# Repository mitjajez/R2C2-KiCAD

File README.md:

R2C2 - RepRapCncController ver. KiCAD
==========

Original design made by FMendes75@gmail.com

https://github.com/bitboxelectronics/R2C2_Hardware/blob/master/v1.2/R2C2_v1.2_Schematics.pdf

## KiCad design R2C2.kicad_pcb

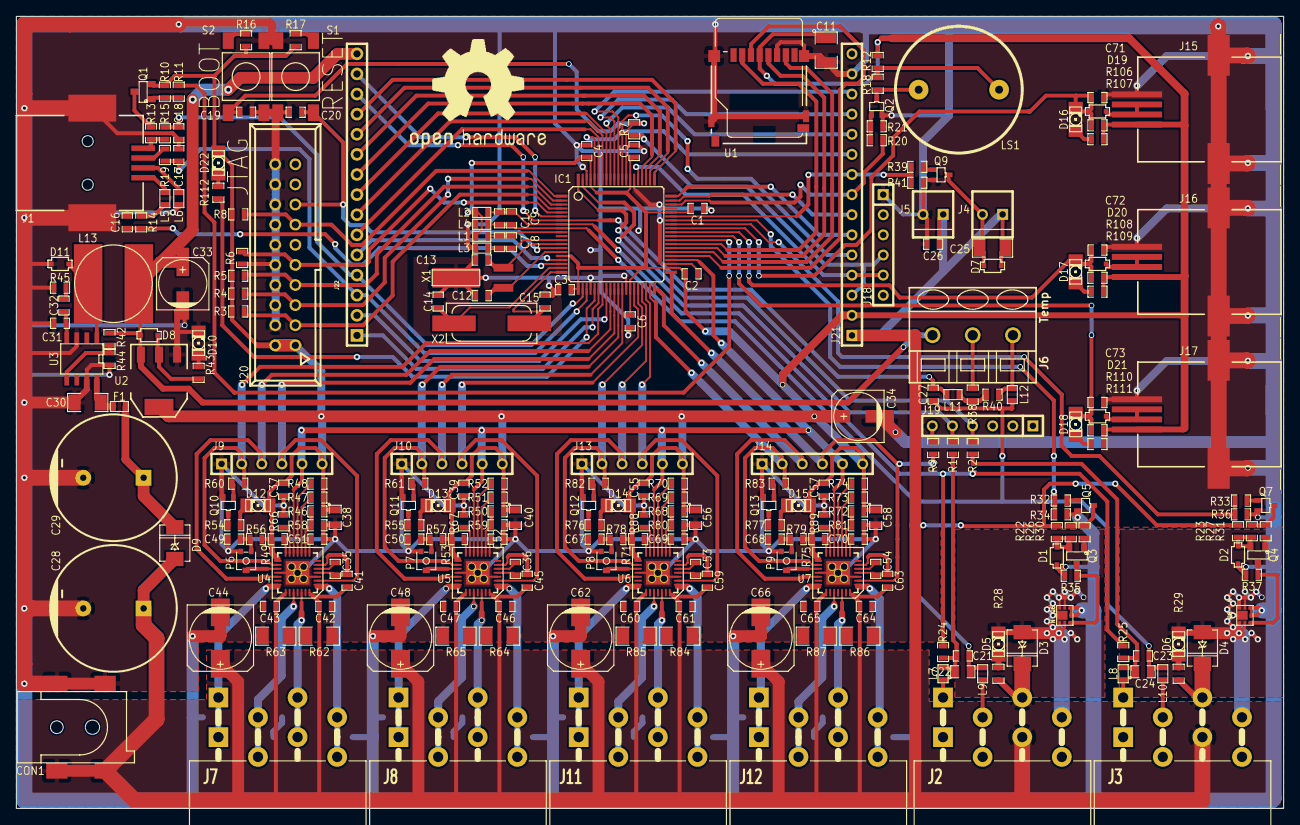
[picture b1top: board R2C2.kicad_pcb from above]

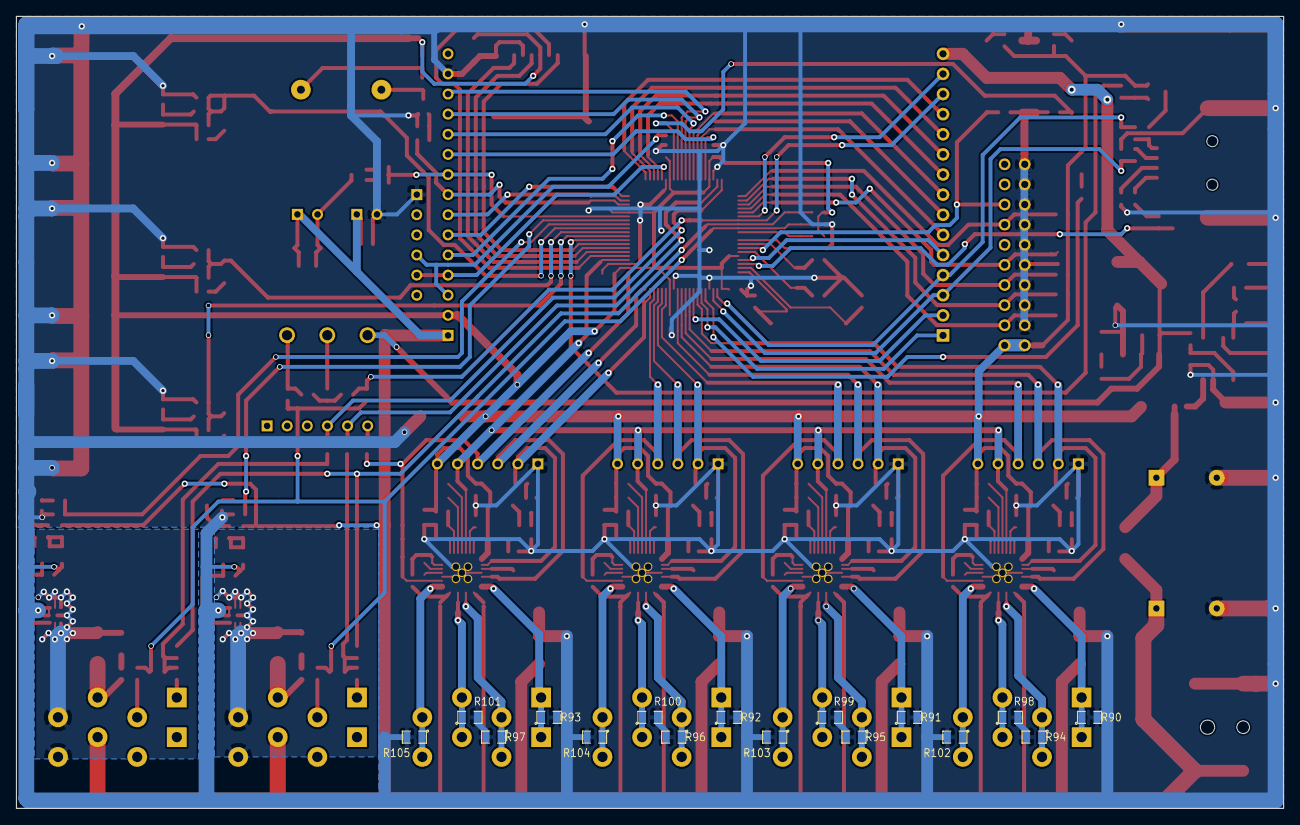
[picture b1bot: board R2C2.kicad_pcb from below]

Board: 2 copper layers, 160.0 x 100.0 mm, 274 parts (16 on the bottom side), 201 nets.

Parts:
C1, C2, C3, C4, C5, C6, C16, C19, C20, C21, C23, C26, C27, C35, C36, C37, C39, C41, C42, C43, C45, C46, C47, C49, C50, C53, C54, C55, C57, C59, C60, C61, C63, C64, C65, C67, C68: 100nF; SM0603_Capa
C7, C10: 1nF; SM0603_Capa
C8, C9, C71, C72, C73: 10nF; SM0603_Capa
C11: 47uF 6.3V; SM1210
C12, C13, C14, C15, C17, C18: 22pF; SM0603_Capa
C22, C24, C38, C40, C56, C58: 10uF 6.3V; SM0805
C25, C30: 10uF 35V; SM1206
C28, C29: 2200uF 35V; CP_16x25mm
C31: 220pF; SM0603_Capa
C32: 22nF; SM0603_Capa
C33, C34: 100uF 10V; c_elec_6.3x5.3
C44, C48, C62, C66: 100uF 50V; c_elec_8x10
C51, C52, C69, C70: 220nF; SM0603_Capa
CON1: BARREL_JACK; SMPowerSocket
D1, D2: 12V; SOD323(F)
D3, D4, D9: 60V@1.5A; DO-214AA(SMB)
D5, D6, D12, D13, D14, D15: Red; LED-1206
D7, D8: 30V@1A; SOD323(F)
D10: Orange; LED-1206
D11: 25V@2A; SOD323(F)
D16, D17, D18: Green; LED-1206
D19, D20, D21: SCH; SOD323(F)
D22: Blue; LED-1206
F1: 3.15A; SM0603
IC1: LPC1758; LQFP80-SOT315
J1: USB; USB_B_smd
J2: CTC1; RAST5-4
J3: CTC2; RAST5-4
J4: Ext Fan; conn-22-29-2021
J5: Drv Fan; conn-22-29-2021
J6: Temp; SMKDSN-3
J7: X; RAST5-4
J8: Y; RAST5-4
J9, J10, J13, J14, J18, J19: HDR1X6H; HDR1X6V
J11: Z; RAST5-4
J12: E; RAST5-4
J15, J16, J17: RJ11; RJ11_6-4_smd
J20: JTAG; VASCH10x2
J21, J22: EXPANSION; SIL-15
L1, L2, L3, L4, L5, L6, L7, L8, L9, L10, L11, L12: 470R@100MHz; SM0603
L13: 33uH 1.5Adc; SDR1006
LS1: Buzzer; BUZZER
P6, P7, P8, P9: 10k; PVZ2A
Q1, Q3, Q4: P; SOT23
Q2, Q5, Q7, Q9, Q10, Q11, Q12, Q13: N; SOT323
Q6, Q8: N; SOT1220
R1, R2, R30, R31, R32, R33, R39: 100R; SM0603_Resistor
R3, R4, R5, R6, R8, R11, R14, R34, R35, R36, R37, R40, R41, R46, R47, R48, R49, R50, R51, R52, R53, R66, R67, R68, R69, R70, R71, R72, R73, R74, R75, R88, R89, R106, R108, R110: 10k; SM0603_Resistor
R7, R9, R12, R13, R18, R22, R23: 1k5; SM0603_Resistor
R10, R21: 1M; SM0603_Resistor
R15, R19: 33R; SM0603_Resistor
R16, R17, R20, R26, R27, R58, R59, R60, R61, R80, R81, R82, R83: 100k; SM0603_Resistor
R24, R25, R54, R55, R76, R77, R107, R109, R111: 274R; SM0603_Resistor
R28, R29, R45: 4k7; SM0603_Resistor
R38, R42: 6k8 1%; SM0603_Resistor
R43, R112: 680R; SM0603_Resistor
R44: 2k2 1%; SM0603_Resistor
R56, R57, R78, R79: 39k; SM0603_Resistor
R62, R63, R64, R65, R84, R85, R86, R87: 0R047; SM1206
R90, R91, R92, R93, R94, R95, R96, R97, R98, R99, R100, R101, R102, R103, R104, R105: 6k8; SM0805
S1: BOOT; SW_SMD
S2: RESET; SW_SMD
U1: CONN_MICROSD; SDCARD-DM3D-SF
U2: 1117; SOT223
U3: L5970D; SO8E
U4, U5, U6, U7: A4988; QFN28
X1: 32.768kHz; Q_AB26TR
X2: 12MHz; Q_HC-49_SM

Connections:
+3.3V: C1.1, C2.1, C3.1, C4.1, C5.1, C6.1, C11.1, C34.1, C37.1, C38.1, C39.1, C40.1, C55.1, C56.1, C57.1, C58.1, D8.1, D12.1, D13.1, D14.1, D15.1, D22.1, IC1.16, IC1.21, IC1.34, IC1.42, IC1.56, IC1.67, IC1.77, J9.6, J10.6, J13.6, J14.6, J15.1, J16.1, J17.1, J20.1, J20.2, J21.2, L1.1, L2.1, Q1.S, R3.1, R4.1, R5.1, R8.1, R10.1, R12.1, R16.1, R17.1, R43.1, R46.1, R47.1, R48.1, R49.1, R50.1, R51.1, R52.1, R53.1, R56.1, R57.1, R68.1, R69.1, R70.1, R71.1, R72.1, R73.1, R74.1, R75.1, R78.1, R79.1, R106.1, R107.1, R108.1, R109.1, R110.1, R111.1, U1.4, U2.2, U4.15, U5.15, U6.15, U7.15
+3.3VADC: C9.1, C10.1, IC1.8, L2.2, R24.1, R25.1
+5V: C33.1, D8.2, J6.1, J22.15, L13.2, R42.1, U2.3
/Motor drivers/E_Motor_1A: J12.2, R97.1, U7.24
/Motor drivers/E_Motor_1B: J12.1, R93.1, U7.21
/Motor drivers/E_Motor_2A: J12.3, R101.1, U7.26
/Motor drivers/E_Motor_2B: J12.4, R105.1, U7.1
/Motor drivers/X_Motor_1A: J7.2, R94.1, U4.24
/Motor drivers/X_Motor_1B: J7.1, R90.1, U4.21
/Motor drivers/X_Motor_2A: J7.3, R98.1, U4.26
/Motor drivers/X_Motor_2B: J7.4, R102.1, U4.1
/Motor drivers/Y_Motor_1A: J8.2, R95.1, U5.24
/Motor drivers/Y_Motor_1B: J8.1, R91.1, U5.21
/Motor drivers/Y_Motor_2A: J8.3, R99.1, U5.26
/Motor drivers/Y_Motor_2B: J8.4, R103.1, U5.1
/Motor drivers/Z_Motor_1A: J11.2, R96.1, U6.24
/Motor drivers/Z_Motor_1B: J11.1, R92.1, U6.21
/Motor drivers/Z_Motor_2A: J11.3, R100.1, U6.26
/Motor drivers/Z_Motor_2B: J11.4, R104.1, U6.1
/Processing core/*BUSB: C19.1, IC1.68, R7.1, R16.2, S1.2
/Processing core/*RST: C20.1, IC1.14, J20.15, R17.2, S2.2
/Processing core/*TRST: IC1.4, J20.3, R3.2
/Processing core/*USB_PPWR: IC1.26, J22.1
/Processing core/DBG_RXD: J18.4, J21.3, R7.2
/Processing core/DBG_TXD: IC1.65, J18.5, J21.4
/Processing core/EXP_AD1_P1.31: IC1.17, J22.5
/Processing core/EXP_AD3_AOUT_P0.26: IC1.6, J22.14
/Processing core/EXP_IO1_P1.15: IC1.69, J21.5
/Processing core/EXP_IO2_P1.0: IC1.76, J21.10
/Processing core/EXP_IO3_P1.9: IC1.72, J21.11
/Processing core/EXP_IO4_P1.10: IC1.71, J21.12
/Processing core/EXP_IO5_P1.14: IC1.70, J21.13
/Processing core/EXP_IO6_P1.1: IC1.75, J22.6
/Processing core/EXP_IO7_P1.4: IC1.74, J22.7
/Processing core/EXP_IO8_P1.8: IC1.73, J22.8
/Processing core/EXP_MISO1_P0.8: IC1.62, J22.11
/Processing core/EXP_MOSI1_P0.9: IC1.61, J22.12
/Processing core/EXP_PWM1_TXD1_P2.0: IC1.60, J21.6
/Processing core/EXP_PWM2_RXD1_P2.1: IC1.59, J21.7
/Processing core/EXP_PWM3_Buzzer_P2.2: IC1.58, J21.8, R20.1
/Processing core/EXP_SCK1_P0.7: IC1.63, J22.10
/Processing core/EXP_SSEL1_P0.6: IC1.64, J22.9
/Processing core/RTS: J19.6, R9.2
/Processing core/RXD0: IC1.80, J19.4, R2.2
/Processing core/SD_MISO0: IC1.46, U1.7
/Processing core/SD_MOSI0: IC1.45, U1.3
/Processing core/SD_SCK0: IC1.47, U1.5
/Processing core/SD_SSEL0: IC1.48, U1.2
/Processing core/TCK: IC1.5, J20.9, R6.2
/Processing core/TDI: IC1.2, J20.5, R4.2
/Processing core/TDO: IC1.1, J20.13, R8.2
/Processing core/TMS: IC1.3, J20.7, R5.2
/Processing core/TXD0: IC1.79, J19.5, R1.2
/Processing core/USB_Connect: IC1.49, R11.2
/Processing core/USB_D_n: C17.1, IC1.23, J22.3, R19.2
/Processing core/USB_D_p: C18.1, IC1.22, J22.4, R15.2
/Processing core/USB_PWR: IC1.28, J22.2
/Processing core/USB_Up_LED: IC1.25, R112.1
/Processing core/USB_Vbus: C16.1, IC1.18, R14.1
/Temperature regulation/CTC1_NTC1: J2.1, L7.2
/Temperature regulation/CTC1_NTC2: J2.2, L9.2
/Temperature regulation/CTC2_NTC1: J3.1, L8.2
/Temperature regulation/CTC2_NTC2: J3.2, L10.2
CTC1_Heat: IC1.54, R32.1, R34.1
CTC1_Temp: C21.1, C22.1, L7.1, R1.1, R24.2
CTC2_Heat: IC1.53, R33.1, R36.1
CTC2_Temp: C23.1, C24.1, L8.1, R2.1, R25.2
GND: C1.2, C2.2, C3.2, C4.2, C5.2, C6.2, C11.2, C12.2, C13.2, C14.2, C15.2, C16.2, C17.2, C18.2, C19.2, C20.2, C26.2, C28.2, C29.2, C30.2, C31.2, C33.2, C34.2, C37.2, C38.2, C39.2, C40.2, C42.2, C43.2, C44.2, C46.2, C47.2, C48.2, C49.2, C50.2, C51.2, C52.2, C55.2, C56.2, C57.2, C58.2, C60.2, C61.2, C62.2, C64.2, C65.2, C66.2, C67.2, C68.2, C69.2, C70.2, C71.2, C72.2, C73.2, CON1.2, D1.1, D2.1, D10.2, D11.1, IC1.24, IC1.33, IC1.43, IC1.57, IC1.66, IC1.78, J1.5, J1.6, J5.2, J9.1, J10.1, J13.1, J14.1, J15.4, J16.4, J17.4, J18.1, J20.4, J20.6, J20.8, J20.10, J20.12, J20.14, J20.16, J20.18, J20.20, J21.14, L3.1, L4.1, L6.1, P6.3, P7.3, P8.3, P9.3, Q2.S, Q5.S, Q6.S, Q7.S, Q8.S, Q9.S, Q10.S, Q11.S, Q12.S, Q13.S, R6.1, R21.2, R34.2, R35.2, R36.2, R37.2, R41.2, R44.2, R45.2, R58.2, R59.2, R62.2, R63.2, R64.2, R65.2, R66.2, R67.2, R80.2, R81.2, R84.2, R85.2, R86.2, R87.2, R88.2, R89.2, R90.2, R91.2, R92.2, R93.2, R94.2, R95.2, R96.2, R97.2, R98.2, R99.2, R100.2, R101.2, R102.2, R103.2, R104.2, R105.2, S1.1, S2.1, U1.6, U2.1, U3.3, U3.7, U4.3, U4.18, U5.3, U5.18, U6.3, U6.18, U7.3, U7.18
GNDPWR: C9.2, C10.2, C21.2, C22.2, C23.2, C24.2, C27.2, IC1.9, L4.2, L9.1, L10.1, L12.1
ME_DIR: IC1.40, J14.3, U7.19
ME_EN: IC1.41, J14.4, R9.1, U7.2
ME_STEP: IC1.39, J14.2, R83.2, U7.16
MX_DIR: IC1.29, J9.3, U4.19
MX_EN: IC1.30, J9.4, U4.2
MX_STEP: IC1.27, J9.2, R60.2, U4.16
MY_DIR: IC1.32, J10.3, U5.19
MY_EN: IC1.35, J10.4, U5.2
MY_STEP: IC1.31, J10.2, R61.2, U5.16
MZ_DIR: IC1.37, J13.3, U6.19
MZ_EN: IC1.38, J13.4, U6.2
MZ_STEP: IC1.36, J13.2, R82.2, U6.16
Mn_RST: IC1.44, J9.5, J10.5, J13.5, J14.5, U4.12, U5.12, U6.12, U7.12
unnamed: J1.4, L6.2
unnamed: L5.1, R14.2
unnamed: J1.2, R19.1
unnamed: J1.3, R13.2, R15.1
unnamed: J1.1, L5.2
unnamed: Q1.D, R13.1
unnamed: Q1.G, R10.2, R11.1
unnamed: Q2.G, R20.2, R21.1
unnamed: LS1.1, R12.2, R18.1
unnamed: LS1.2, Q2.D, R18.2
unnamed: D22.2, R112.2
unnamed: C14.1, IC1.19, X2.1
unnamed: C15.1, IC1.20, X2.2
unnamed: C13.1, IC1.13, X1.2
unnamed: C7.2, C8.2, IC1.12, L3.2
unnamed: C7.1, C8.1, IC1.10, L1.2
unnamed: C12.1, IC1.15, X1.1
unnamed: D5.1, R28.2
unnamed: D3.1, D5.2, J2.4, Q6.D
unnamed: D1.2, Q3.S, R22.1, R26.1
unnamed: D4.1, D6.2, J3.4, Q8.D
unnamed: D2.2, Q4.S, R23.1, R27.1
unnamed: Q7.D, R27.2, R31.1
unnamed: Q4.D, Q8.G, R37.1
unnamed: Q4.G, R31.2
unnamed: Q7.G, R33.2
unnamed: D6.1, R29.2
unnamed: Q9.G, R39.2
unnamed: C25.2, D7.1, J4.2, Q9.D
unnamed: Q3.G, R30.2
unnamed: Q5.G, R32.2
unnamed: Q3.D, Q6.G, R35.1
unnamed: Q5.D, R26.2, R30.1
unnamed: J6.2, R38.2
unnamed: L11.2, R38.1, R40.1
unnamed: J6.3, L12.2, R40.2
unnamed: D17.1, R109.2
unnamed: D18.1, R111.2
unnamed: D21.2, J17.2, J17.3
unnamed: D16.1, R107.2
unnamed: D19.2, J15.2, J15.3
unnamed: D20.2, J16.2, J16.3
unnamed: Q10.D, R54.2
unnamed: Q10.G, R60.1
unnamed: R62.1, U4.27
unnamed: R63.1, U4.23
unnamed: C51.1, U4.8
unnamed: C35.2, U4.5
unnamed: C41.2, U4.6
unnamed: C35.1, U4.4
unnamed: D13.2, R55.1
unnamed: R50.2, R59.1, U5.9
unnamed: C49.1, P6.1, R56.2
unnamed: R66.1, U4.13
unnamed: R51.2, U5.10
unnamed: R53.2, U5.14
unnamed: C50.1, P7.1, R57.2
unnamed: P7.2, U5.17
unnamed: R52.2, U5.11
unnamed: R48.2, U4.11
unnamed: C54.2, U7.5
unnamed: C54.1, U7.4
unnamed: C63.2, U7.6
unnamed: P9.2, U7.17
unnamed: R87.1, U7.23
unnamed: R86.1, U7.27
unnamed: D12.2, R54.1
unnamed: R46.2, R58.1, U4.9
unnamed: R47.2, U4.10
unnamed: R49.2, U4.14
unnamed: P6.2, U4.17
unnamed: R72.2, R81.1, U7.9
unnamed: C70.1, U7.8
unnamed: R74.2, U7.11
unnamed: R73.2, U7.10
unnamed: R75.2, U7.14
unnamed: C67.1, P8.1, R78.2
unnamed: R88.1, U6.13
unnamed: C68.1, P9.1, R79.2
unnamed: D15.2, R77.1
unnamed: Q13.D, R77.2
unnamed: Q13.G, R83.1
unnamed: R89.1, U7.13
unnamed: Q11.D, R55.2
unnamed: Q11.G, R61.1
unnamed: R67.1, U5.13
unnamed: R64.1, U5.27
unnamed: R65.1, U5.23
unnamed: C52.1, U5.8
unnamed: C36.2, U5.5
unnamed: C45.2, U5.6
unnamed: C36.1, U5.4
unnamed: C53.2, U6.5
unnamed: C53.1, U6.4
unnamed: C59.2, U6.6
unnamed: Q12.D, R76.2
unnamed: Q12.G, R82.1
unnamed: R71.2, U6.14
unnamed: P8.2, U6.17
unnamed: R70.2, U6.11
unnamed: R69.2, U6.10
unnamed: R68.2, R80.1, U6.9
unnamed: D14.2, R76.1
unnamed: C69.1, U6.8
unnamed: R84.1, U6.27
unnamed: R85.1, U6.23
unnamed: C29.1, D9.2, F1.1
unnamed: C30.1, F1.2, U3.8
unnamed: D10.1, R43.2
unnamed: C32.2, R45.1
unnamed: C31.1, C32.1, U3.4
unnamed: R42.2, R44.1, U3.5
unnamed: D11.2, L13.1, U3.1
Opto_X: C71.1, D16.2, D19.1, IC1.52, R106.2
Opto_Y: C72.1, D17.2, D20.1, IC1.51, R108.2
Opto_Z: C73.1, D18.2, D21.1, IC1.50, R110.2
PWM_FAN: IC1.55, J21.9, R39.1, R41.1
Thermocouple: C27.1, IC1.7, J22.13, L11.1
VMEM: C25.1, C26.1, C28.1, C41.1, C42.1, C43.1, C44.1, C45.1, C46.1, C47.1, C48.1, C59.1, C60.1, C61.1, C62.1, C63.1, C64.1, C65.1, C66.1, CON1.1, D3.2, D4.2, D7.2, D9.1, J2.3, J3.3, J4.1, J5.1, J21.1, R22.2, R23.2, R28.1, R29.1, U4.22, U4.28, U5.22, U5.28, U6.22, U6.28, U7.22, U7.28
